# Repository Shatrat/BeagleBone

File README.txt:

Forking Toby Corkindale's excellent Beaglebone Perl modules in order to add some functionality.
Namely, adding support for OLED displays on the SSD1306 other than 128x32 sequential.
Adding the ability to easily put the display to sleep and wake it back up.

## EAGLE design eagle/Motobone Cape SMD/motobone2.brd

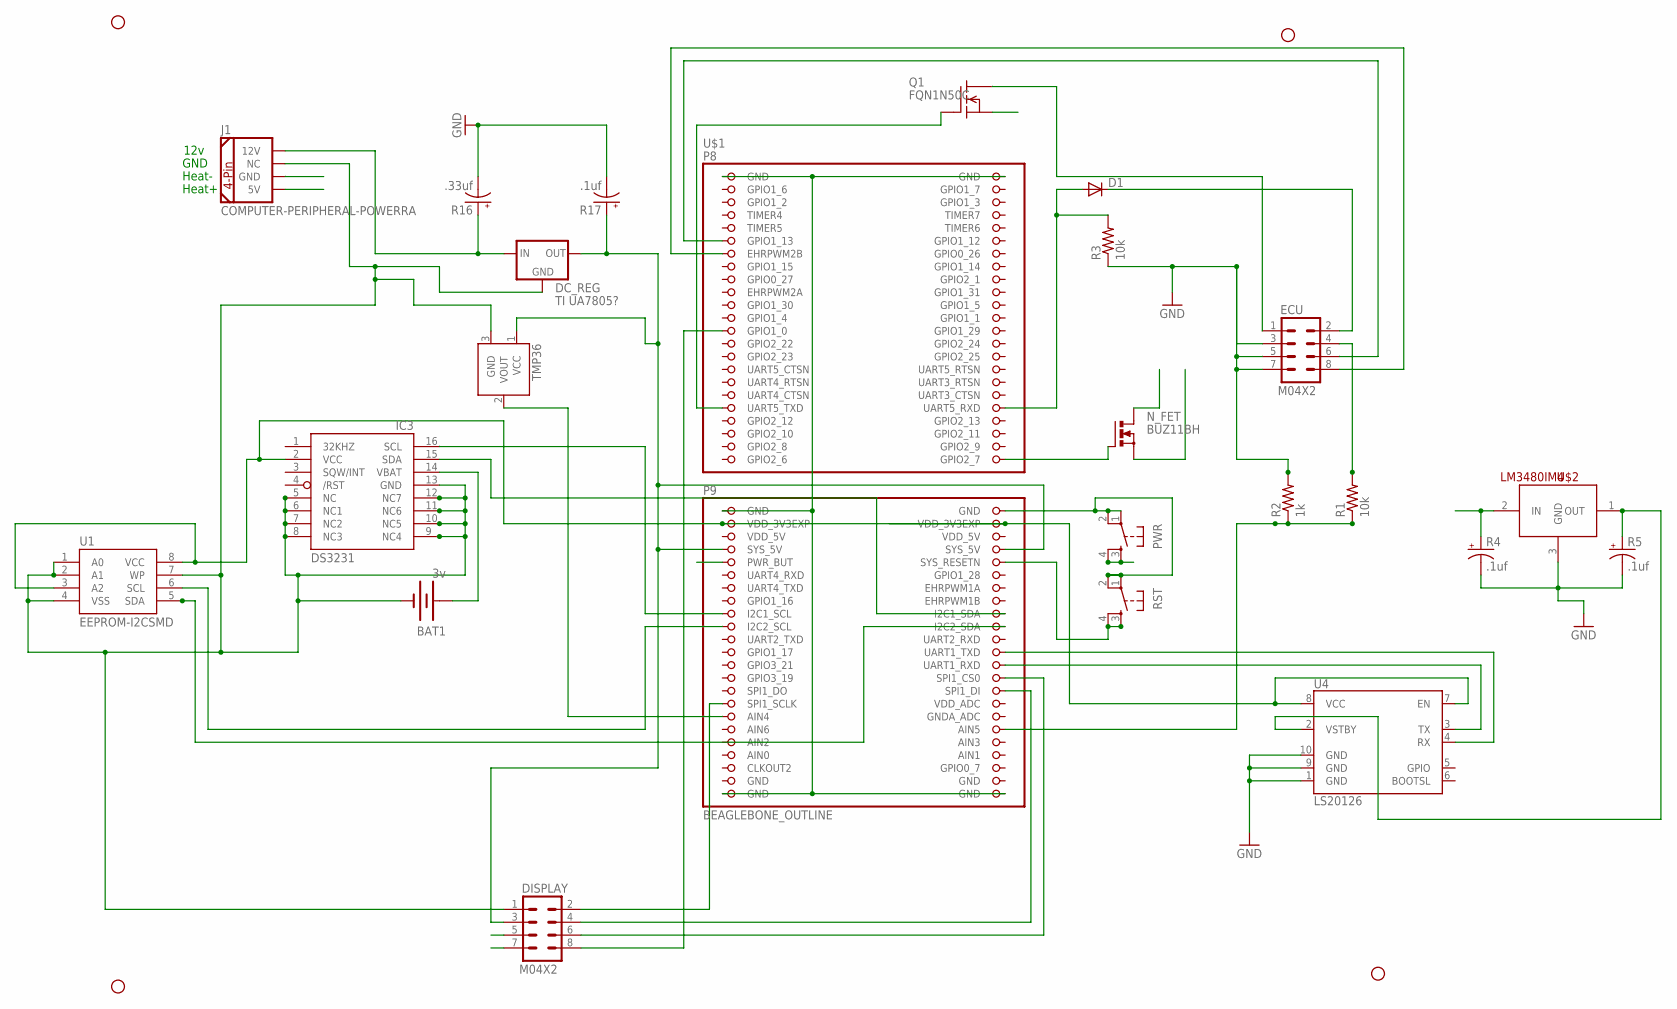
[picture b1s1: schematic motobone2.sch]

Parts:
BAT1: 3v; BATTCON_12MM_PTH
D1: DIODE1N4148; DIODE-1N4148
DC_REG: TI UA7805?; 78XXL
DISPLAY: M04X2; 2X4
ECU: M04X2; 2X4
IC3: DS3231/SO; SO16W
J1: COMPUTER-PERIPHERAL-POWERRA; COMPUTER-PERIPHERAL-POWER-RA
N_FET: BUZ11BH; TO220BH
PWR: TAC_SWITCHPTH; TACTILE-PTH
Q1: FQN1N50C; TO92
R1, R3: 10k; 1206
R2: 1k; 1206
R4, R5, R17: .1uf; EIA3216
R16: .33uf; EIA3216
RST: TAC_SWITCHPTH; TACTILE-PTH
STANDOFF1, STANDOFF2, STANDOFF3, STANDOFF4: STAND-OFF
TMP36: TMP36GT9; TO-92
U1: EEPROM-I2CSMD; SO08
U4: LS20126
U$1: BEAGLEBONE_OUTLINE; BEAGLEBONE_SHIELD
U$2: LM3480IM4; SOT23-3

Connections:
12V: DC_REG.IN, J1.12V, R4.A (+), R16.A (+), U$2.2 (IN)
12V_ECU: ECU.4, R1.2
AIN0: U$1.85 (AIN0)
GND: BAT1.GND (-), DC_REG.GND, DISPLAY.1, ECU.3, ECU.5, ECU.7, IC3.5 (NC), IC3.6 (NC1), IC3.7 (NC2), IC3.8 (NC3), IC3.9 (NC4), IC3.10 (NC5), IC3.11 (NC6), IC3.12 (NC7), IC3.13 (GND), J1.NC, PWR.1, PWR.2, R2.2, R3.1, R4.C (-), R5.C (-), R16.C (-), R17.C (-), RST.1, RST.2, TMP36.3 (GND), U1.1 (A0), U1.2 (A1), U1.4 (VSS), U1.7 (WP), U4.1 (GND), U4.9 (GND), U4.10 (GND), U$1.1 (GND), U$1.2 (GND), U$1.47 (GND), U$1.48 (GND), U$1.89 (GND), U$1.90 (GND), U$1.91 (GND), U$1.92 (GND), U$2.3 (GND)
HEAT+: J1.5V, N_FET.S
HEAT-: J1.GND, N_FET.D
HEAT_GPIO: N_FET.G, U$1.46 (GPIO2_7)
unnamed: DISPLAY.4, U$1.76 (SPI1_DI)
unnamed: IC3.16 (SCL), U$1.63 (I2C1_SCL)
unnamed: DISPLAY.2, U$1.77 (SPI1_SCLK)
unnamed: TMP36.2 (VOUT), U$1.79 (AIN4)
unnamed: BAT1.VCC@1 (+), IC3.14 (VBAT)
unnamed: R5.A (+), U4.2 (VSTBY), U$2.1 (OUT)
unnamed: IC3.15 (SDA), U$1.64 (I2C1_SDA)
unnamed: U1.6 (SCL), U$1.65 (I2C2_SCL)
unnamed: U1.5 (SDA), U$1.66 (I2C2_SDA)
unnamed: DISPLAY.6, U$1.74 (SPI1_CS0)
unnamed: Q1.1 (G), U$1.37 (UART5_TXD)
unnamed: ECU.6, U$1.11 (GPIO1_13)
unnamed: ECU.8, U$1.13 (EHRPWM2B)
unnamed: U4.3 (TX), U$1.72 (UART1_RXD)
unnamed: R1.1, R2.1, U$1.82 (AIN5)
unnamed: U4.4 (RX), U$1.70 (UART1_TXD)
unnamed: DISPLAY.8, U$1.25 (GPIO1_0)
unnamed: D1.C, ECU.2
unnamed: D1.A, R3.2, U$1.38 (UART5_RXD)
unnamed: ECU.1, Q1.2 (D)
PWR_BTN: DISPLAY.7, PWR.3, PWR.4, U$1.55 (PWR_BUT)
RST_BTN: DISPLAY.5, RST.3, RST.4, U$1.56 (SYS_RESETN)
SYS_5V: DC_REG.OUT, DISPLAY.3, Q1.3 (S), R17.A (+), TMP36.1 (VCC), U$1.53 (SYS_5V), U$1.54 (SYS_5V)
VDD_3V3: IC3.2 (VCC), U1.3 (A2), U1.8 (VCC), U4.7 (EN), U4.8 (VCC), U$1.49 (VDD_3V3EXP), U$1.50 (VDD_3V3EXP)
VDD_5V: U$1.51 (VDD_5V), U$1.52 (VDD_5V)

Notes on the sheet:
12v
GND
Heat-
Heat+

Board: 2 copper layers, 27 parts (0 on the bottom side), 31 nets, no tracks yet.

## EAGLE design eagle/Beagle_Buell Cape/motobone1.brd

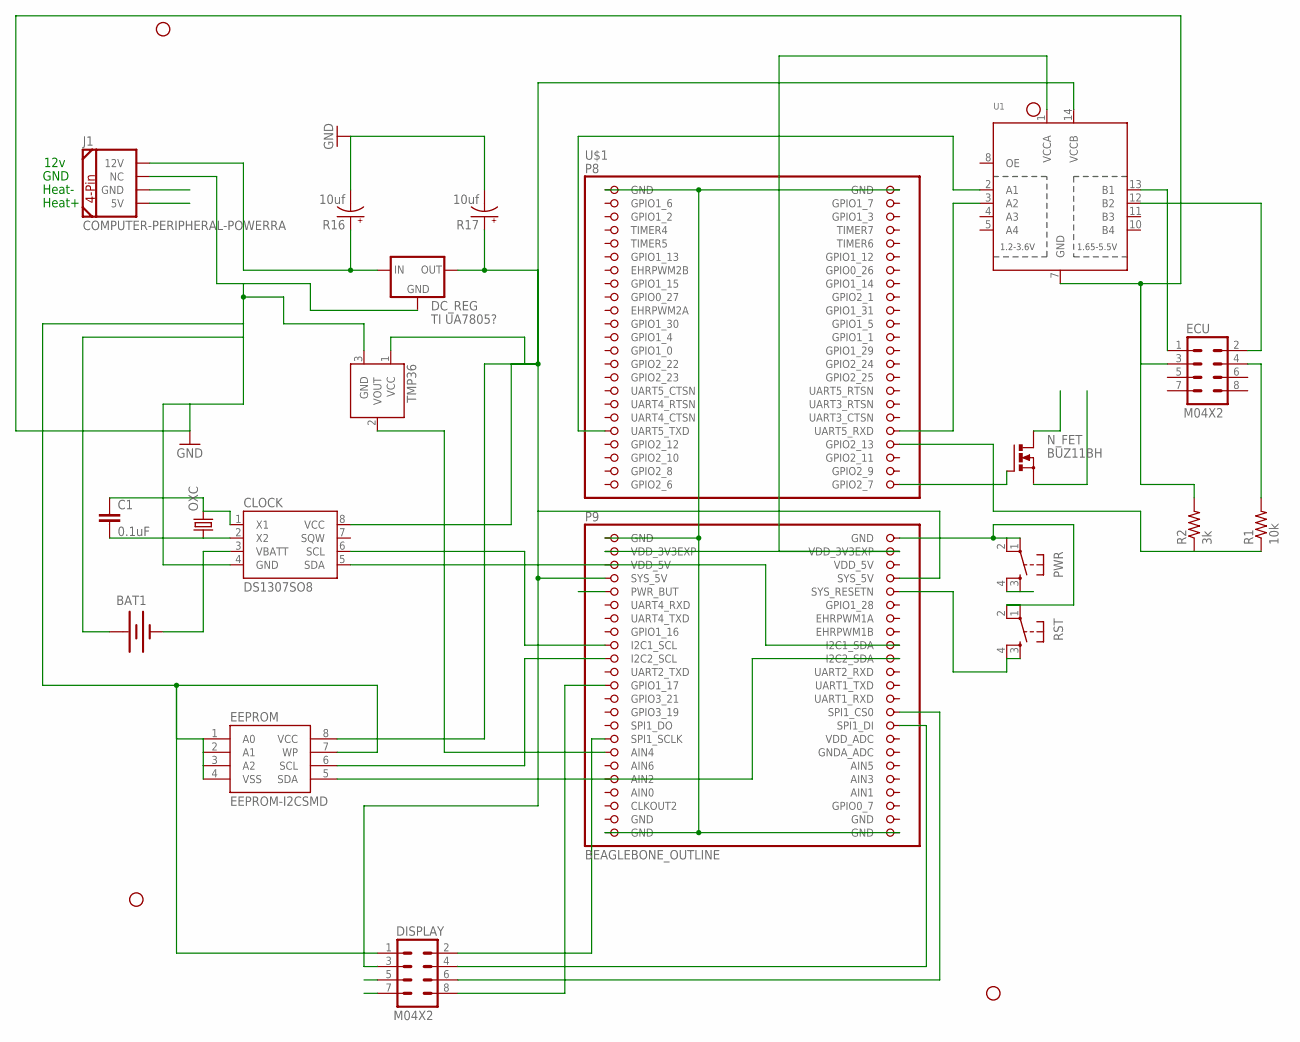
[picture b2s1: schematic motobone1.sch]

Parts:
BAT1: BATTERY12PTH; BATTCON_12MM_PTH
C1: 0.1uF; 1206
CLOCK: DS1307SO8; SO08
DC_REG: TI UA7805?; 78XXL
DISPLAY: M04X2; 2X4
ECU: M04X2; 2X4
EEPROM: EEPROM-I2CSMD; SO08
J1: COMPUTER-PERIPHERAL-POWERRA; COMPUTER-PERIPHERAL-POWER-RA
N_FET: BUZ11BH; TO220BH
OXC: CRYSTALTC38H; TC38H
PWR: TAC_SWITCHPTH; TACTILE-PTH
R1: 10k; 1206
R2: 3k; 1206
R16, R17: 10uf; EIA3216
RST: TAC_SWITCHPTH; TACTILE-PTH
STANDOFF1, STANDOFF2, STANDOFF3, STANDOFF4: STAND-OFF
TMP36: TMP36GT9; TO-92
U1: TXB0104PWRSOIC14; SO14
U$1: BEAGLEBONE_OUTLINE; BEAGLEBONE_SHIELD

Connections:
12V: DC_REG.IN, J1.12V, R16.A (+)
12V_ECU: ECU.4, R1.2
AIN0: U$1.85 (AIN0)
GND: BAT1.VCC@1 (+), CLOCK.4 (GND), DC_REG.GND, DISPLAY.1, ECU.3, EEPROM.1 (A0), EEPROM.2 (A1), EEPROM.3 (A2), EEPROM.4 (VSS), EEPROM.7 (WP), J1.NC, PWR.1, PWR.2, R2.2, R16.C (-), R17.C (-), RST.1, RST.2, TMP36.3 (GND), U1.7 (GND), U$1.48 (GND), U$1.89 (GND), U$1.90 (GND)
HEAT+: J1.5V, N_FET.S
HEAT-: J1.GND, N_FET.D
HEAT_GPIO: N_FET.G, U$1.46 (GPIO2_7)
unnamed: DISPLAY.4, U$1.76 (SPI1_DI)
unnamed: CLOCK.6 (SCL), U$1.63 (I2C1_SCL)
unnamed: DISPLAY.2, U$1.77 (SPI1_SCLK)
unnamed: TMP36.2 (VOUT), U$1.79 (AIN4)
unnamed: C1.2, CLOCK.2 (X2), OXC.1
unnamed: C1.1, CLOCK.1 (X1), OXC.2
unnamed: CLOCK.5 (SDA), U$1.64 (I2C1_SDA)
unnamed: BAT1.GND (-), CLOCK.3 (VBATT)
unnamed: EEPROM.6 (SCL), U$1.65 (I2C2_SCL)
unnamed: EEPROM.5 (SDA), U$1.66 (I2C2_SDA)
unnamed: DISPLAY.6, U$1.74 (SPI1_CS0)
unnamed: U$1.1 (GND), U$1.2 (GND), U$1.47 (GND), U$1.91 (GND), U$1.92 (GND)
unnamed: R1.1, R2.1, U$1.40 (GPIO2_13)
unnamed: DISPLAY.8, U$1.69 (GPIO1_17)
unnamed: ECU.1, U1.13 (B1)
unnamed: ECU.2, U1.12 (B2)
unnamed: U1.3 (A2), U$1.38 (UART5_RXD)
unnamed: U1.2 (A1), U$1.37 (UART5_TXD)
PWR_BTN: DISPLAY.7, PWR.3, PWR.4, U$1.55 (PWR_BUT)
RST_BTN: DISPLAY.5, RST.3, RST.4, U$1.56 (SYS_RESETN)
SYS_5V: CLOCK.8 (VCC), DC_REG.OUT, DISPLAY.3, EEPROM.8 (VCC), R17.A (+), TMP36.1 (VCC), U1.14 (VCCB), U$1.53 (SYS_5V), U$1.54 (SYS_5V)
VDD_3V3: U1.1 (VCCA), U$1.49 (VDD_3V3EXP), U$1.50 (VDD_3V3EXP)
VDD_5V: U$1.51 (VDD_5V), U$1.52 (VDD_5V)

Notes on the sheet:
12v
GND
Heat-
Heat+

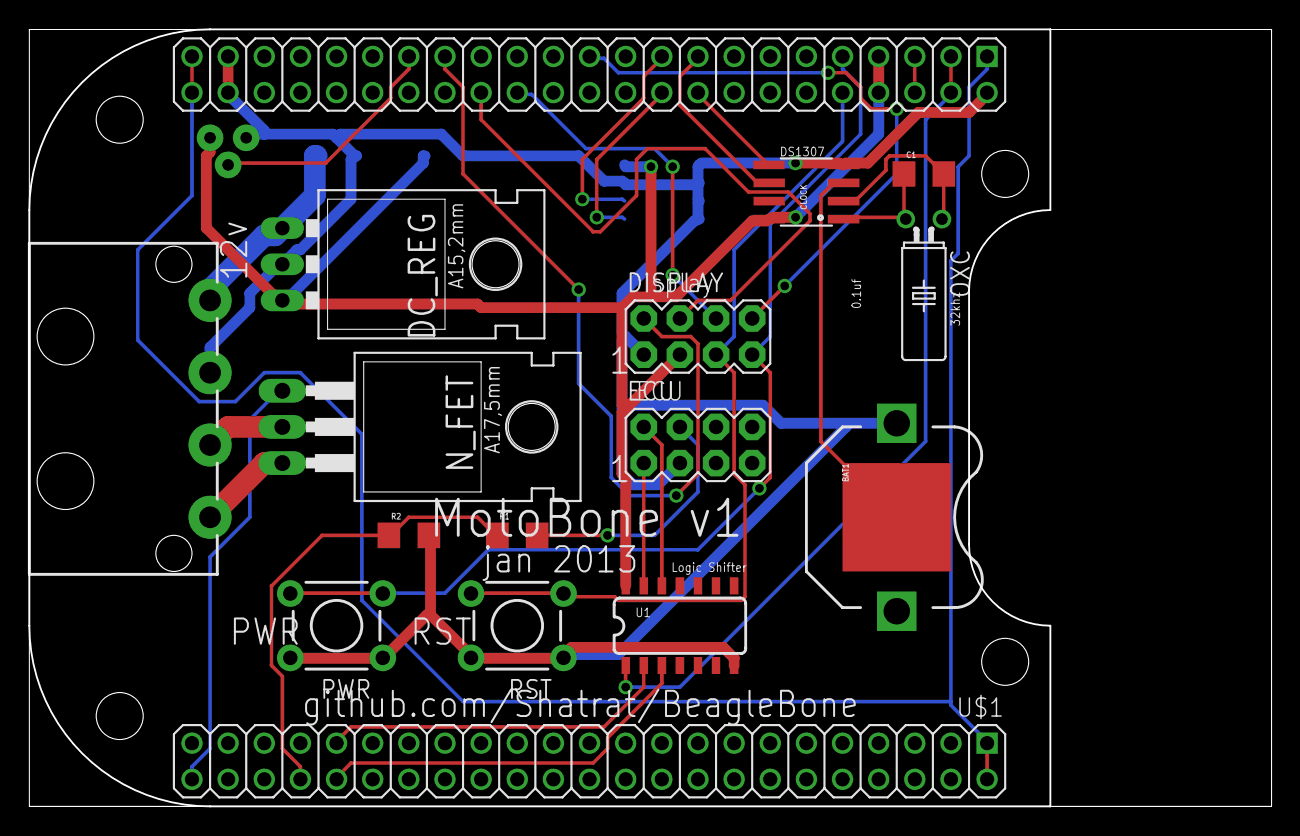
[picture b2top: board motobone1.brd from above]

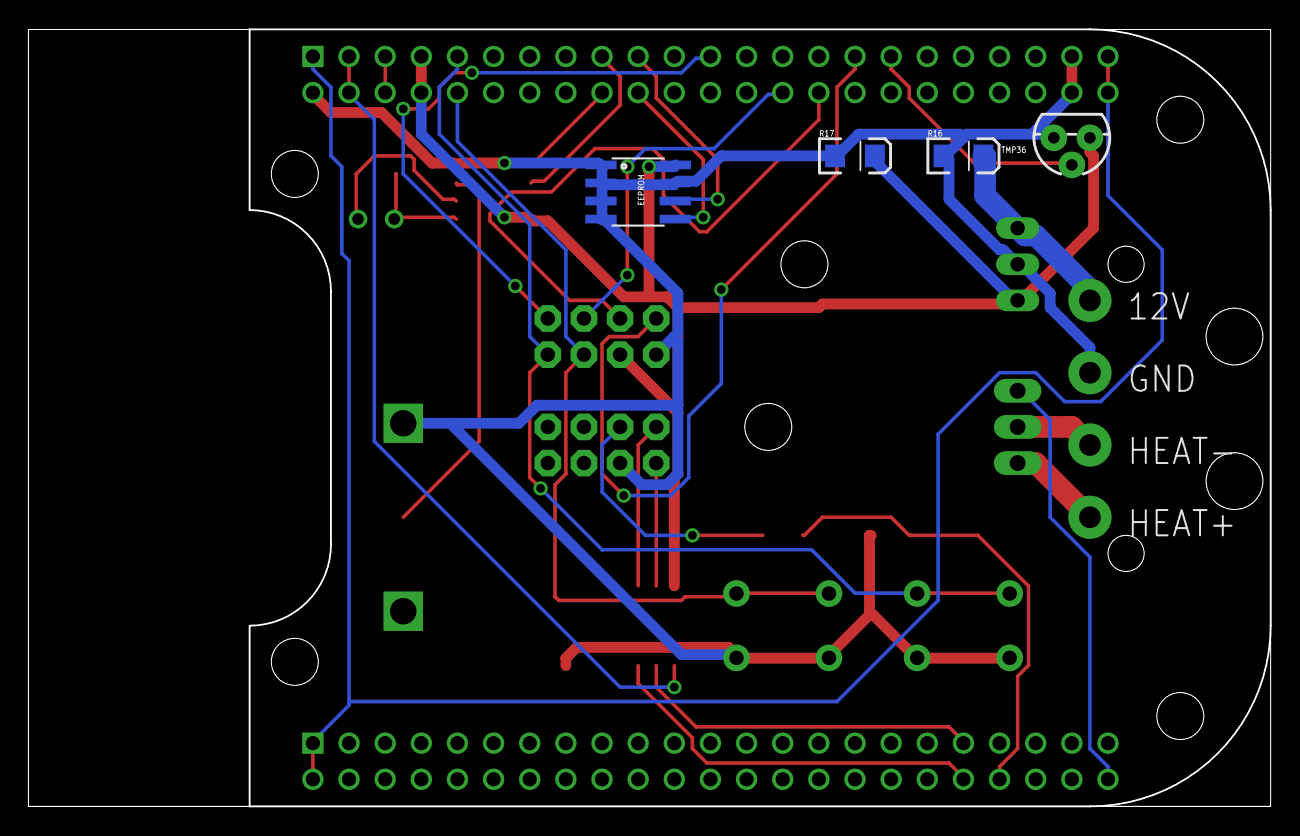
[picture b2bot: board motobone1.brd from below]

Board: 2 copper layers, 87.2 x 54.6 mm, 23 parts (4 on the bottom side), 29 nets.

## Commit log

2013-01-17 Uploading changes from local work to forked source on Github
2013-01-17 Update perl/beagle_buell_imager.pl
    Edited some comments for clarity
2013-01-17 Added some more testing to try to resolve my frame 1+ corruption issues
2013-01-17 Adding comments
2013-01-20 updating from local BBone copy
2013-01-21 updating all changes from local copy
2013-01-21 more updates from Local
2013-01-21 moved imageToBuffer sub to a new module Image.pm
2013-01-22 updating local changes
2013-01-23 Added some TODO comments for speed increase
2013-01-23 made some efficiency changes to Image.pm
2013-01-24 Updating from local
2013-01-25 added display_image sub
2013-01-26 Made the Image.pm Imager object writing process more object oriented and easier to read
2013-01-27 added subroutine for heated equipment thermostat
2013-01-28 Adding eagle files for beaglebone cape
2013-02-02 updates to Eagle PCB files
2013-02-08 updating Eagle files
2013-02-12 Added serial ECU connection function to beagle_buell_imager.pl

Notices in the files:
parts and their libraries:
SparkFun-Sensors: Licensing: CC v3.0 Share-Alike You are welcome to use this library for commercial purposes.
